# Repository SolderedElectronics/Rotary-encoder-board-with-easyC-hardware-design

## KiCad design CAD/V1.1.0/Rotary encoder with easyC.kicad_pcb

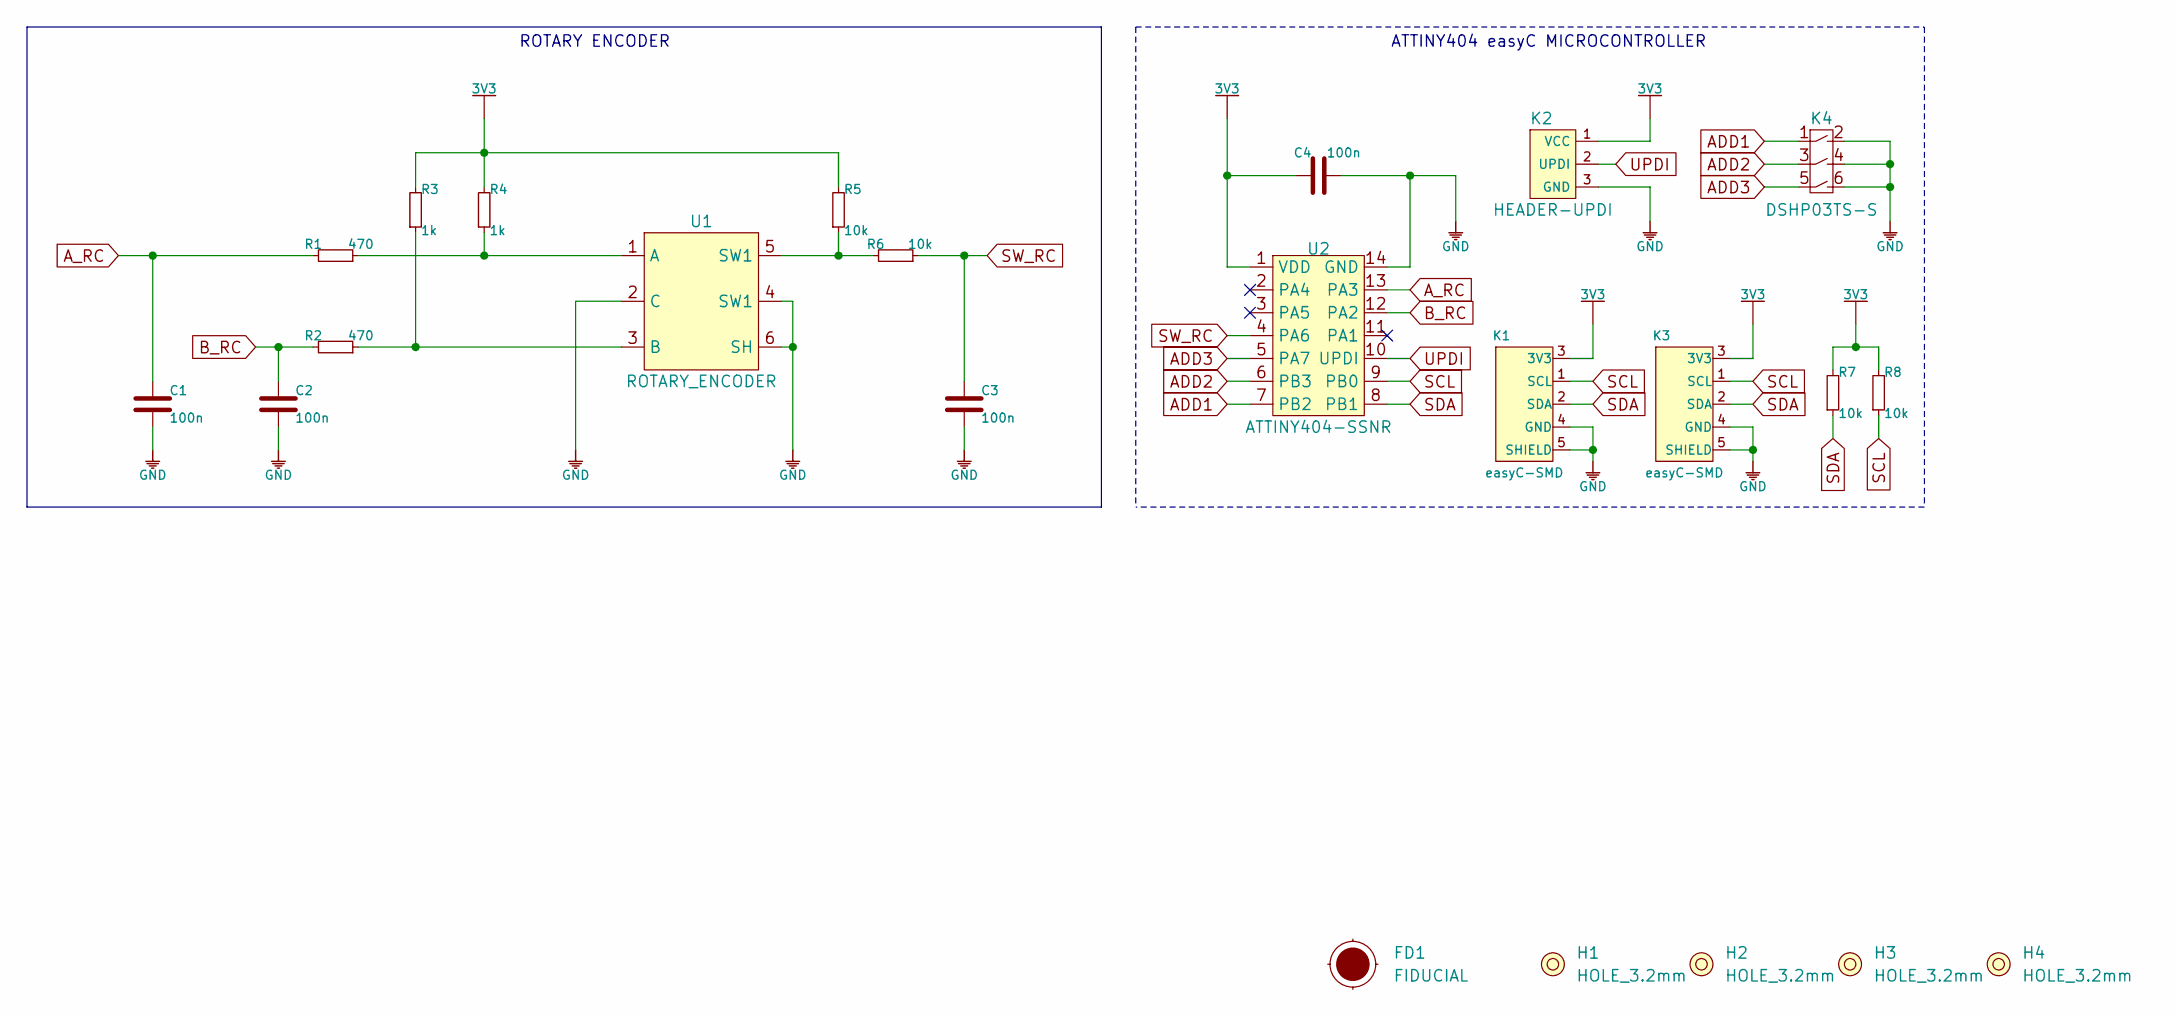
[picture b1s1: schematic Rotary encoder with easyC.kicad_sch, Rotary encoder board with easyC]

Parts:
C1, C2, C3, C4: 100n; 0603C
FD1: FIDUCIAL; FIDUCIAL_23
H1, H2, H3, H4: HOLE_3.2mm
K1, K3: easyC-SMD; easyC-connector
K2: HEADER-UPDI
K4: DSHP03TS-S
R1, R2: 470; 0603R
R3, R4: 1k; 0603R
R5, R6, R7, R8: 10k; 0603R
U1: ROTARY_ENCODER
U2: ATTINY404-SSNR; SOIC-14

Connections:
3V3: C4.1, K1.3 (3V3), K2.1 (VCC), K3.3 (3V3), R3.2, R4.2, R5.2, R7.2, R8.2, U2.1 (VDD)
ADD1: K4.1, U2.7 (PB2)
ADD2: K4.3, U2.6 (PB3)
ADD3: K4.5, U2.5 (PA7)
A_RC: C1.2, R1.2, U2.13 (PA3)
B_RC: C2.2, R2.2, U2.12 (PA2)
GND: C1.1, C2.1, C3.1, C4.2, K1.4 (GND), K1.5 (SHIELD), K2.3 (GND), K3.4 (GND), K3.5 (SHIELD), K4.2, K4.4, K4.6, U1.2 (C), U1.4 (SW1), U1.6 (SH), U2.14 (GND)
unnamed: R1.1, R4.1, U1.1 (A)
unnamed: R2.1, R3.1, U1.3 (B)
unnamed: R5.1, R6.2, U1.5 (SW1)
SCL: K1.1 (SCL), K3.1 (SCL), R8.1, U2.9 (PB0)
SDA: K1.2 (SDA), K3.2 (SDA), R7.1, U2.8 (PB1)
SW_RC: C3.2, R6.1, U2.4 (PA6)
UPDI: K2.2 (UPDI), U2.10 (UPDI)

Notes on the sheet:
ATTINY404 easyC MICROCONTROLLER
ROTARY ENCODER

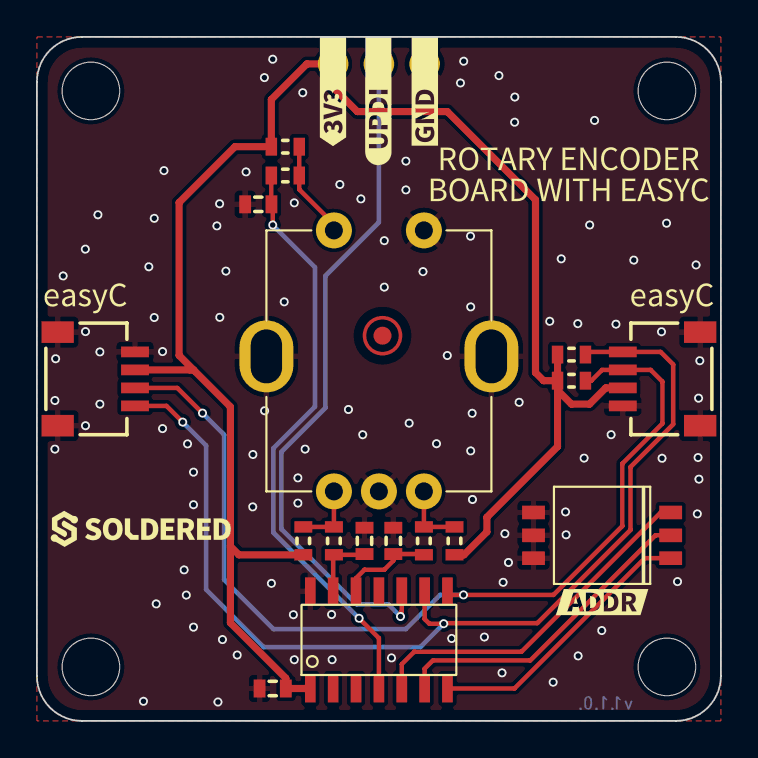
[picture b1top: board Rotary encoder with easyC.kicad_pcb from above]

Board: 2 copper layers, 38.0 x 38.0 mm, 30 parts (1 on the bottom side), 14 nets.

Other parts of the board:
Ref**: Val**; Version1.1.0
kibuzzard-644635E1: G***; kibuzzard-644635E1
kibuzzard-644636D9: G***; kibuzzard-644636D9
kibuzzard-644636FB: G***; kibuzzard-644636FB
kibuzzard-6446370D: G***; kibuzzard-6446370D
kibuzzard-64463666: G***; kibuzzard-64463666
kibuzzard-64664682: G***; kibuzzard-64664682

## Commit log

2022-08-06 Updating open source files.
